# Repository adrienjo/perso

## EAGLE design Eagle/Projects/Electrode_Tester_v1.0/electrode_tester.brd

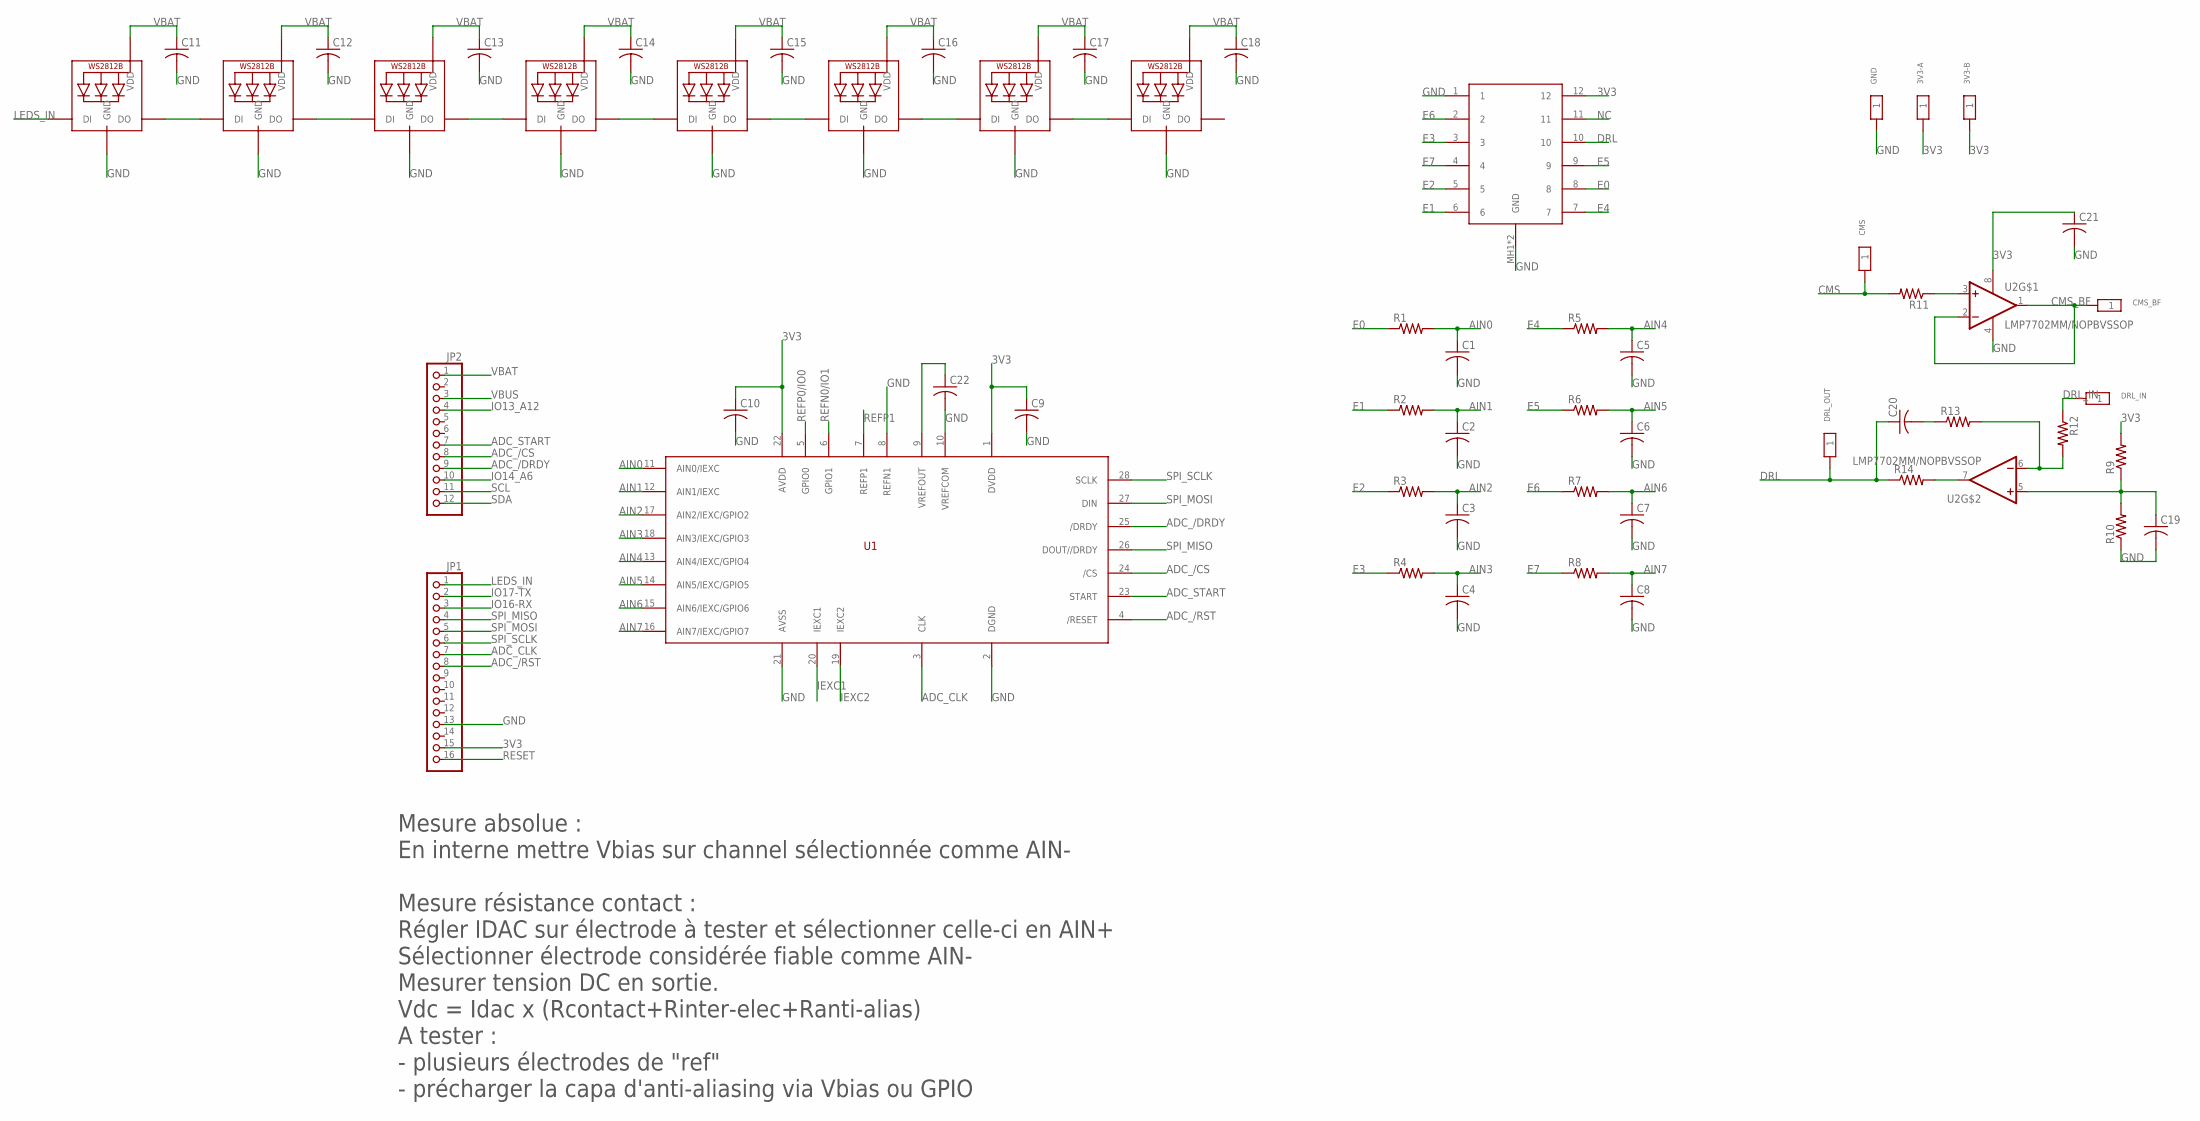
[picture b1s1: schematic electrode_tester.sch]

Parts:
3V3-A, 3V3-B: TESTPAD_PROG; TP1.5MM
C1, C2, C3, C4, C5, C6, C7, C8, C9, C10, C11, C12, C13, C14, C15, C16, C17, C18, C19, C20, C21, C22: C-USC0603; C0603
CMS: TESTPAD_PROG; TP1.5MM
CMS_BF: TESTPAD_PROG; TP1.5MM
CONN1: 505110-1292
DRL_IN: TESTPAD_PROG; TP1.5MM
DRL_OUT: TESTPAD_PROG; TP1.5MM
GND: TESTPAD_PROG; TP1.5MM
JP1: HEADER-1X16ROUND; 1X16_ROUND
JP2: HEADER-1X12; 1X12_ROUND
LED1, LED2, LED3, LED4, LED5, LED6, LED7, LED8: WS2812B5050; WS2812B
R1, R2, R3, R4, R5, R6, R7, R8, R9, R10, R11, R12, R13, R14: R-US_R0603; R0603
U1: ADS1248; TSSOP28
U2: LMP7702MM/NOPBVSSOP; VSSOP8

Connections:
3V3: 3V3-A.1, 3V3-B.1, C9.1, C10.1, C21.1, CONN1.12, JP1.15, R9.2, U1.1 (DVDD), U1.22 (AVDD), U2.8 (V+)
ADC_/CS: JP2.8, U1.24 (/CS)
ADC_/DRDY: JP2.9, U1.25 (/DRDY)
ADC_/RST: JP1.8, U1.4 (/RESET)
ADC_CLK: JP1.7, U1.3 (CLK)
ADC_START: JP2.7, U1.23 (START)
AIN0: C1.1, R1.2, U1.11 (AIN0/IEXC)
AIN1: C2.1, R2.2, U1.12 (AIN1/IEXC)
AIN2: C3.1, R3.2, U1.17 (AIN2/IEXC/GPIO2)
AIN3: C4.1, R4.2, U1.18 (AIN3/IEXC/GPIO3)
AIN4: C5.1, R5.2, U1.13 (AIN4/IEXC/GPIO4)
AIN5: C6.1, R6.2, U1.14 (AIN5/IEXC/GPIO5)
AIN6: C7.1, R7.2, U1.15 (AIN6/IEXC/GPIO6)
AIN7: C8.1, R8.2, U1.16 (AIN7/IEXC/GPIO7)
CMS: CMS.1, R11.2
CMS_BF: CMS_BF.1, U2.1 (OUT), U2.2 (-IN)
DRL: C20.1, CONN1.10, DRL_OUT.1, R14.1
DRL_IN: DRL_IN.1, R12.1
E0: CONN1.8, R1.1
E1: CONN1.6, R2.1
E2: CONN1.5, R3.1
E3: CONN1.3, R4.1
E4: CONN1.7, R5.1
E5: CONN1.9, R6.1
E6: CONN1.2, R7.1
E7: CONN1.4, R8.1
GND: C1.2, C2.2, C3.2, C4.2, C5.2, C6.2, C7.2, C8.2, C9.2, C10.2, C11.2, C12.2, C13.2, C14.2, C15.2, C16.2, C17.2, C18.2, C19.2, C21.2, C22.2, CONN1.1, CONN1.MH1 (GND), CONN1.MH2 (GND), GND.1, JP1.13, LED1.3-GND (GND), LED2.3-GND (GND), LED3.3-GND (GND), LED4.3-GND (GND), LED5.3-GND (GND), LED6.3-GND (GND), LED7.3-GND (GND), LED8.3-GND (GND), R10.1, U1.2 (DGND), U1.8 (REFN1), U1.10 (VREFCOM), U1.21 (AVSS), U2.4 (V-)
IEXC1: U1.20 (IEXC1)
IEXC2: U1.19 (IEXC2)
IO13_A12: JP2.4
IO14_A6: JP2.10
IO16-RX: JP1.3
IO17-TX: JP1.2
LEDS_IN: JP1.1, LED1.4-DIN (DI)
unnamed: LED1.2-DOUT (DO), LED2.4-DIN (DI)
unnamed: LED2.2-DOUT (DO), LED3.4-DIN (DI)
unnamed: LED3.2-DOUT (DO), LED4.4-DIN (DI)
unnamed: LED4.2-DOUT (DO), LED5.4-DIN (DI)
unnamed: LED5.2-DOUT (DO), LED6.4-DIN (DI)
unnamed: LED6.2-DOUT (DO), LED7.4-DIN (DI)
unnamed: LED7.2-DOUT (DO), LED8.4-DIN (DI)
unnamed: R11.1, U2.3 (+IN)
unnamed: C22.1, U1.9 (VREFOUT)
unnamed: R12.2, R13.2, U2.6 (-IN)
unnamed: C20.2, R13.1
unnamed: R14.2, U2.7 (OUT)
unnamed: C19.1, R9.1, R10.2, U2.5 (+IN)
NC: CONN1.11
REFN0/IO1: U1.6 (GPIO1)
REFP0/IO0: U1.5 (GPIO0)
REFP1: U1.7 (REFP1)
RESET: JP1.16
SCL: JP2.11
SDA: JP2.12
SPI_MISO: JP1.4, U1.26 (DOUT//DRDY)
SPI_MOSI: JP1.5, U1.27 (DIN)
SPI_SCLK: JP1.6, U1.28 (SCLK)
VBAT: C11.1, C12.1, C13.1, C14.1, C15.1, C16.1, C17.1, C18.1, JP2.1, LED1.1-VDD (VDD), LED2.1-VDD (VDD), LED3.1-VDD (VDD), LED4.1-VDD (VDD), LED5.1-VDD (VDD), LED6.1-VDD (VDD), LED7.1-VDD (VDD), LED8.1-VDD (VDD)
VBUS: JP2.3

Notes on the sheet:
Mesure absolue : En interne mettre Vbias sur channel sélectionnée comme AIN- Mesure résistance contact : Régler IDAC sur électrode à tester et sélectionner celle-ci en AIN+ Sélectionner électrode considérée fiable comme AIN- Mesurer tension DC en sortie. Vdc = Idac x (Rcontact+Rinter-elec+Ranti-ali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

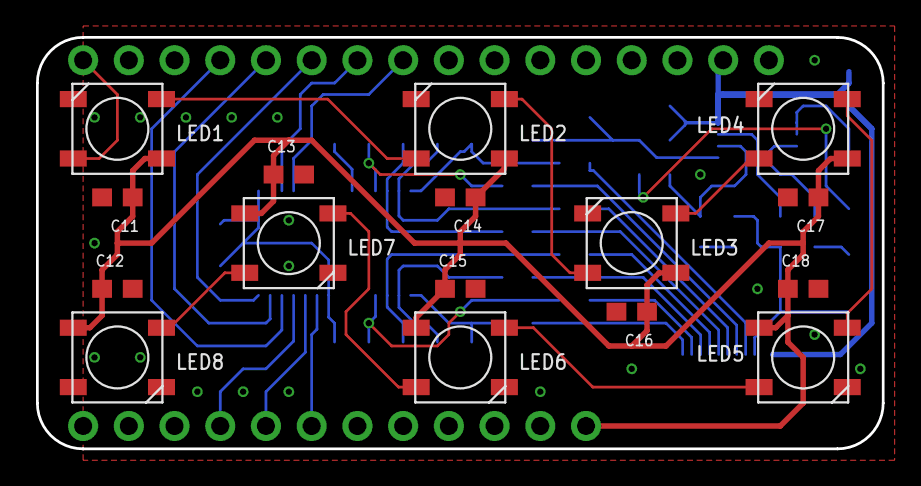
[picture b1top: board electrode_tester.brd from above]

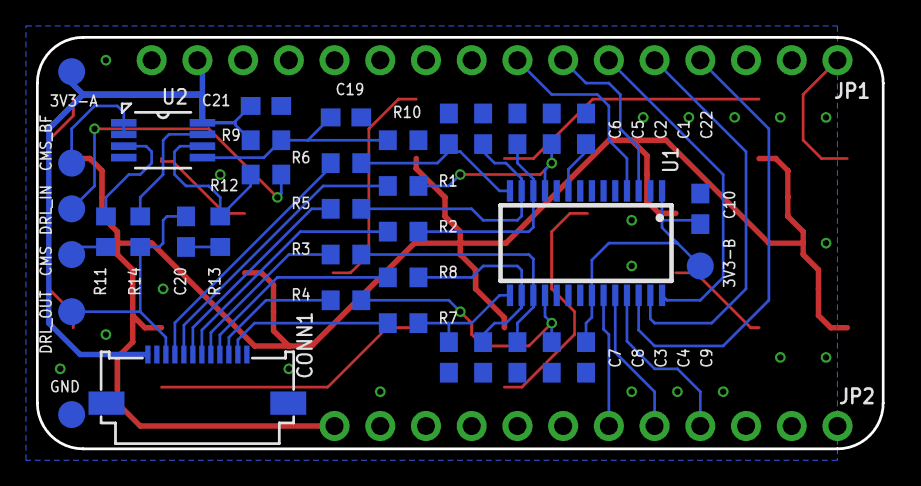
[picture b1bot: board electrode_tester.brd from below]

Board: 2 copper layers, 47.0 x 22.9 mm, 56 parts (40 on the bottom side), 45 nets.

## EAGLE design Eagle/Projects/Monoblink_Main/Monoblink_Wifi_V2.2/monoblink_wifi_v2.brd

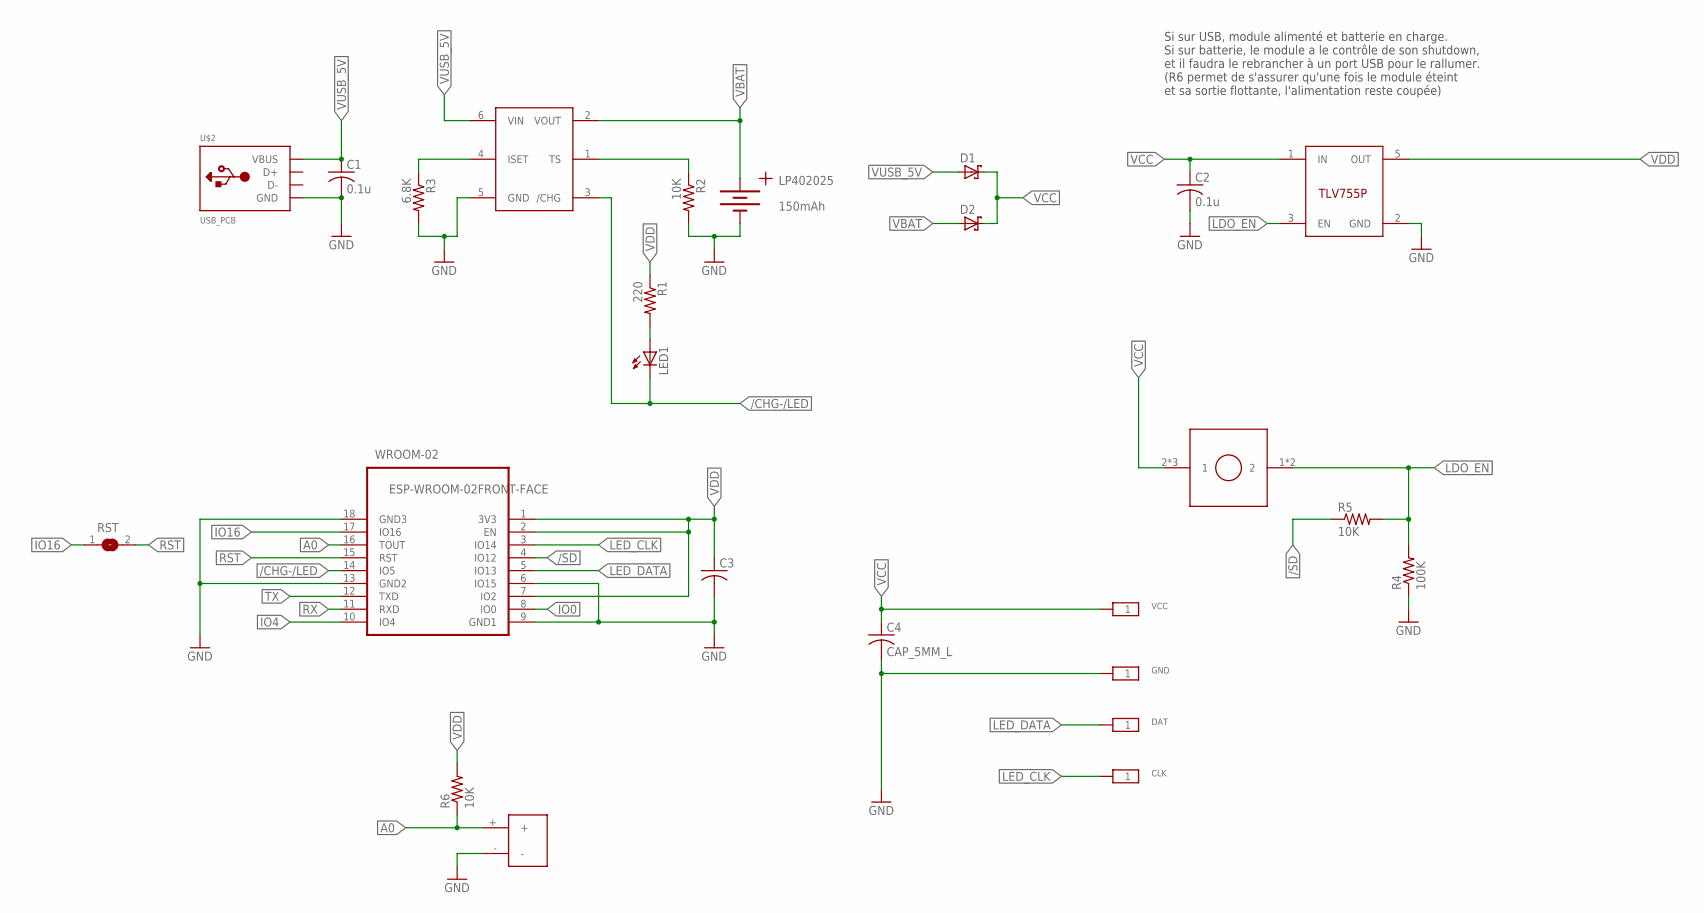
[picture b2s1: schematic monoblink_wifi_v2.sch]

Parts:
C1, C2: 0.1u; C0603
C3: C-USC0603; C0603
C4: CAP_5MM_L; TT2D5L
CHG: BQ21040; SOT23-6
CLK: TESTPAD_PROGSPRING_PIN; MATRIX_CONN
D1, D2: NSR0320MW2T1G; SOD323
DAT: TESTPAD_PROGSPRING_PIN; MATRIX_CONN
GND: TESTPAD_PROGSPRING_PIN; MATRIX_CONN
LDO: TLV755P; SOT23-5
LED1: LEDCHIP-LED0603; CHIP-LED0603
LP402025: 150mAh; BATT_CON
ON/OFF: KMS231GPLFSNO_PEGS; KMS231GLFS
R1: 220; R0603
R2, R5, R6: 10K; R0603
R3: 6.8K; R0603
R4: 100K; R0603
RST: SOLDERJUMPER; SOLDERJUMPER_ARROW_NOPASTE
U$1: 2PIN_STD
U$2: USB_PCB; USB_PADS
VCC: TESTPAD_PROGSPRING_PIN; MATRIX_CONN
WROOM-02: ESP-WROOM-02FRONT-FACE; FRONT-FACE

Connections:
/CHG-/LED: CHG.3 (/CHG), LED1.C, WROOM-02.14 (IO5)
/SD: R5.1, WROOM-02.4 (IO12)
A0: R6.1, U$1.+, WROOM-02.16 (TOUT)
GND: C1.2, C2.2, C3.2, C4.- (2), CHG.5 (GND), GND.1, LDO.2 (GND), LP402025.V- (-), R2.2, R3.2, R4.1, U$1.-, U$2.GND, WROOM-02.6 (IO15), WROOM-02.9 (GND1), WROOM-02.13 (GND2), WROOM-02.18 (GND3)
IO0: WROOM-02.8 (IO0)
IO4: WROOM-02.10 (IO4)
IO16: RST.1, WROOM-02.17 (IO16)
ISET: CHG.4 (ISET), R3.1
LDO_EN: LDO.3 (EN), ON/OFF.1 (2), ON/OFF.5 (2), R4.2, R5.2
LED_CLK: CLK.1, WROOM-02.3 (IO14)
LED_DATA: DAT.1, WROOM-02.5 (IO13)
unnamed: LED1.A, R1.2
RST: RST.2, WROOM-02.15 (RST)
RX: WROOM-02.11 (RXD)
TS: CHG.1 (TS), R2.1
TX: WROOM-02.12 (TXD)
VBAT: CHG.2 (VOUT), D2.2 (A), LP402025.V+ (+)
VCC: C2.1, C4.+ (1), D1.1 (C), D2.1 (C), LDO.1 (IN), ON/OFF.2 (1), ON/OFF.3 (1), ON/OFF.4 (1), VCC.1
VDD: C3.1, LDO.5 (OUT), R1.1, R6.2, WROOM-02.1 (3V3), WROOM-02.2 (EN), WROOM-02.7 (IO2)
VUSB_5V: C1.1, CHG.6 (VIN), D1.2 (A), U$2.V_SUPPLY (VBUS)

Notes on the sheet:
Si sur USB, module alimenté et batterie en charge. Si sur batterie, le module a le contrôle de son shutdown, et il faudra le rebrancher à un port USB pour le rallumer. (R6 permet de s'assurer qu'une fois le module éteint et sa sortie flottante, l'alimentation reste coupée)

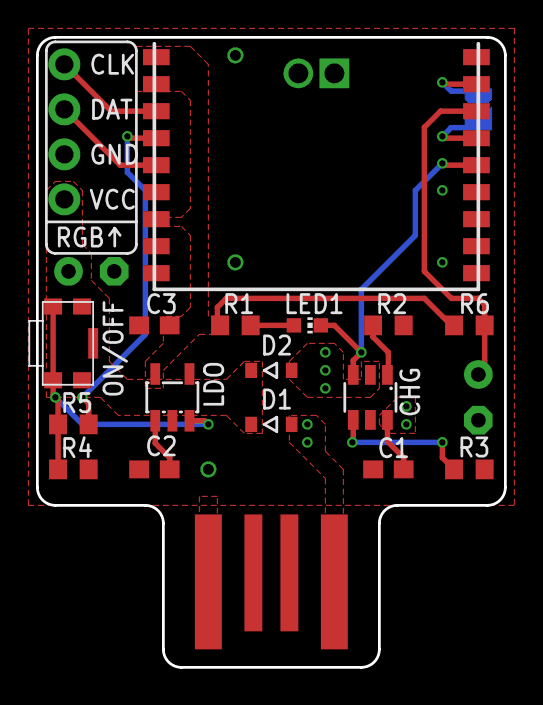
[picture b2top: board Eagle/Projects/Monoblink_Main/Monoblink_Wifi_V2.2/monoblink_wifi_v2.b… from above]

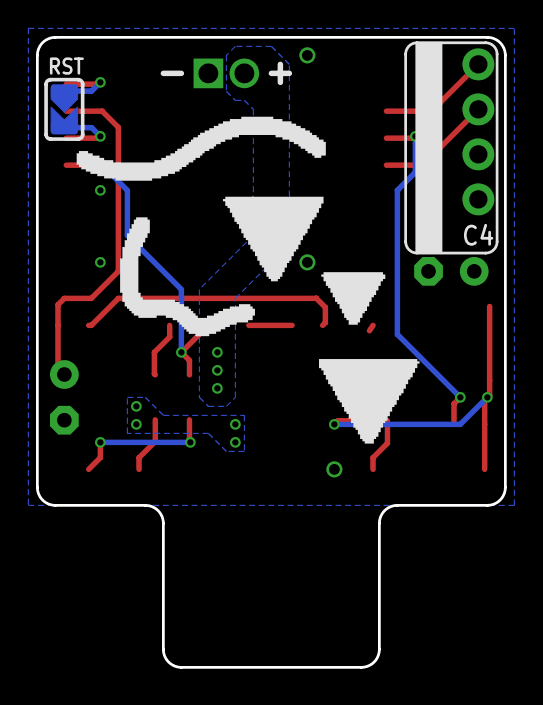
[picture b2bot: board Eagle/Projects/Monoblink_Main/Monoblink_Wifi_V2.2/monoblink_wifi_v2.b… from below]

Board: 2 copper layers, 26.0 x 35.0 mm, 25 parts (2 on the bottom side), 16 nets.

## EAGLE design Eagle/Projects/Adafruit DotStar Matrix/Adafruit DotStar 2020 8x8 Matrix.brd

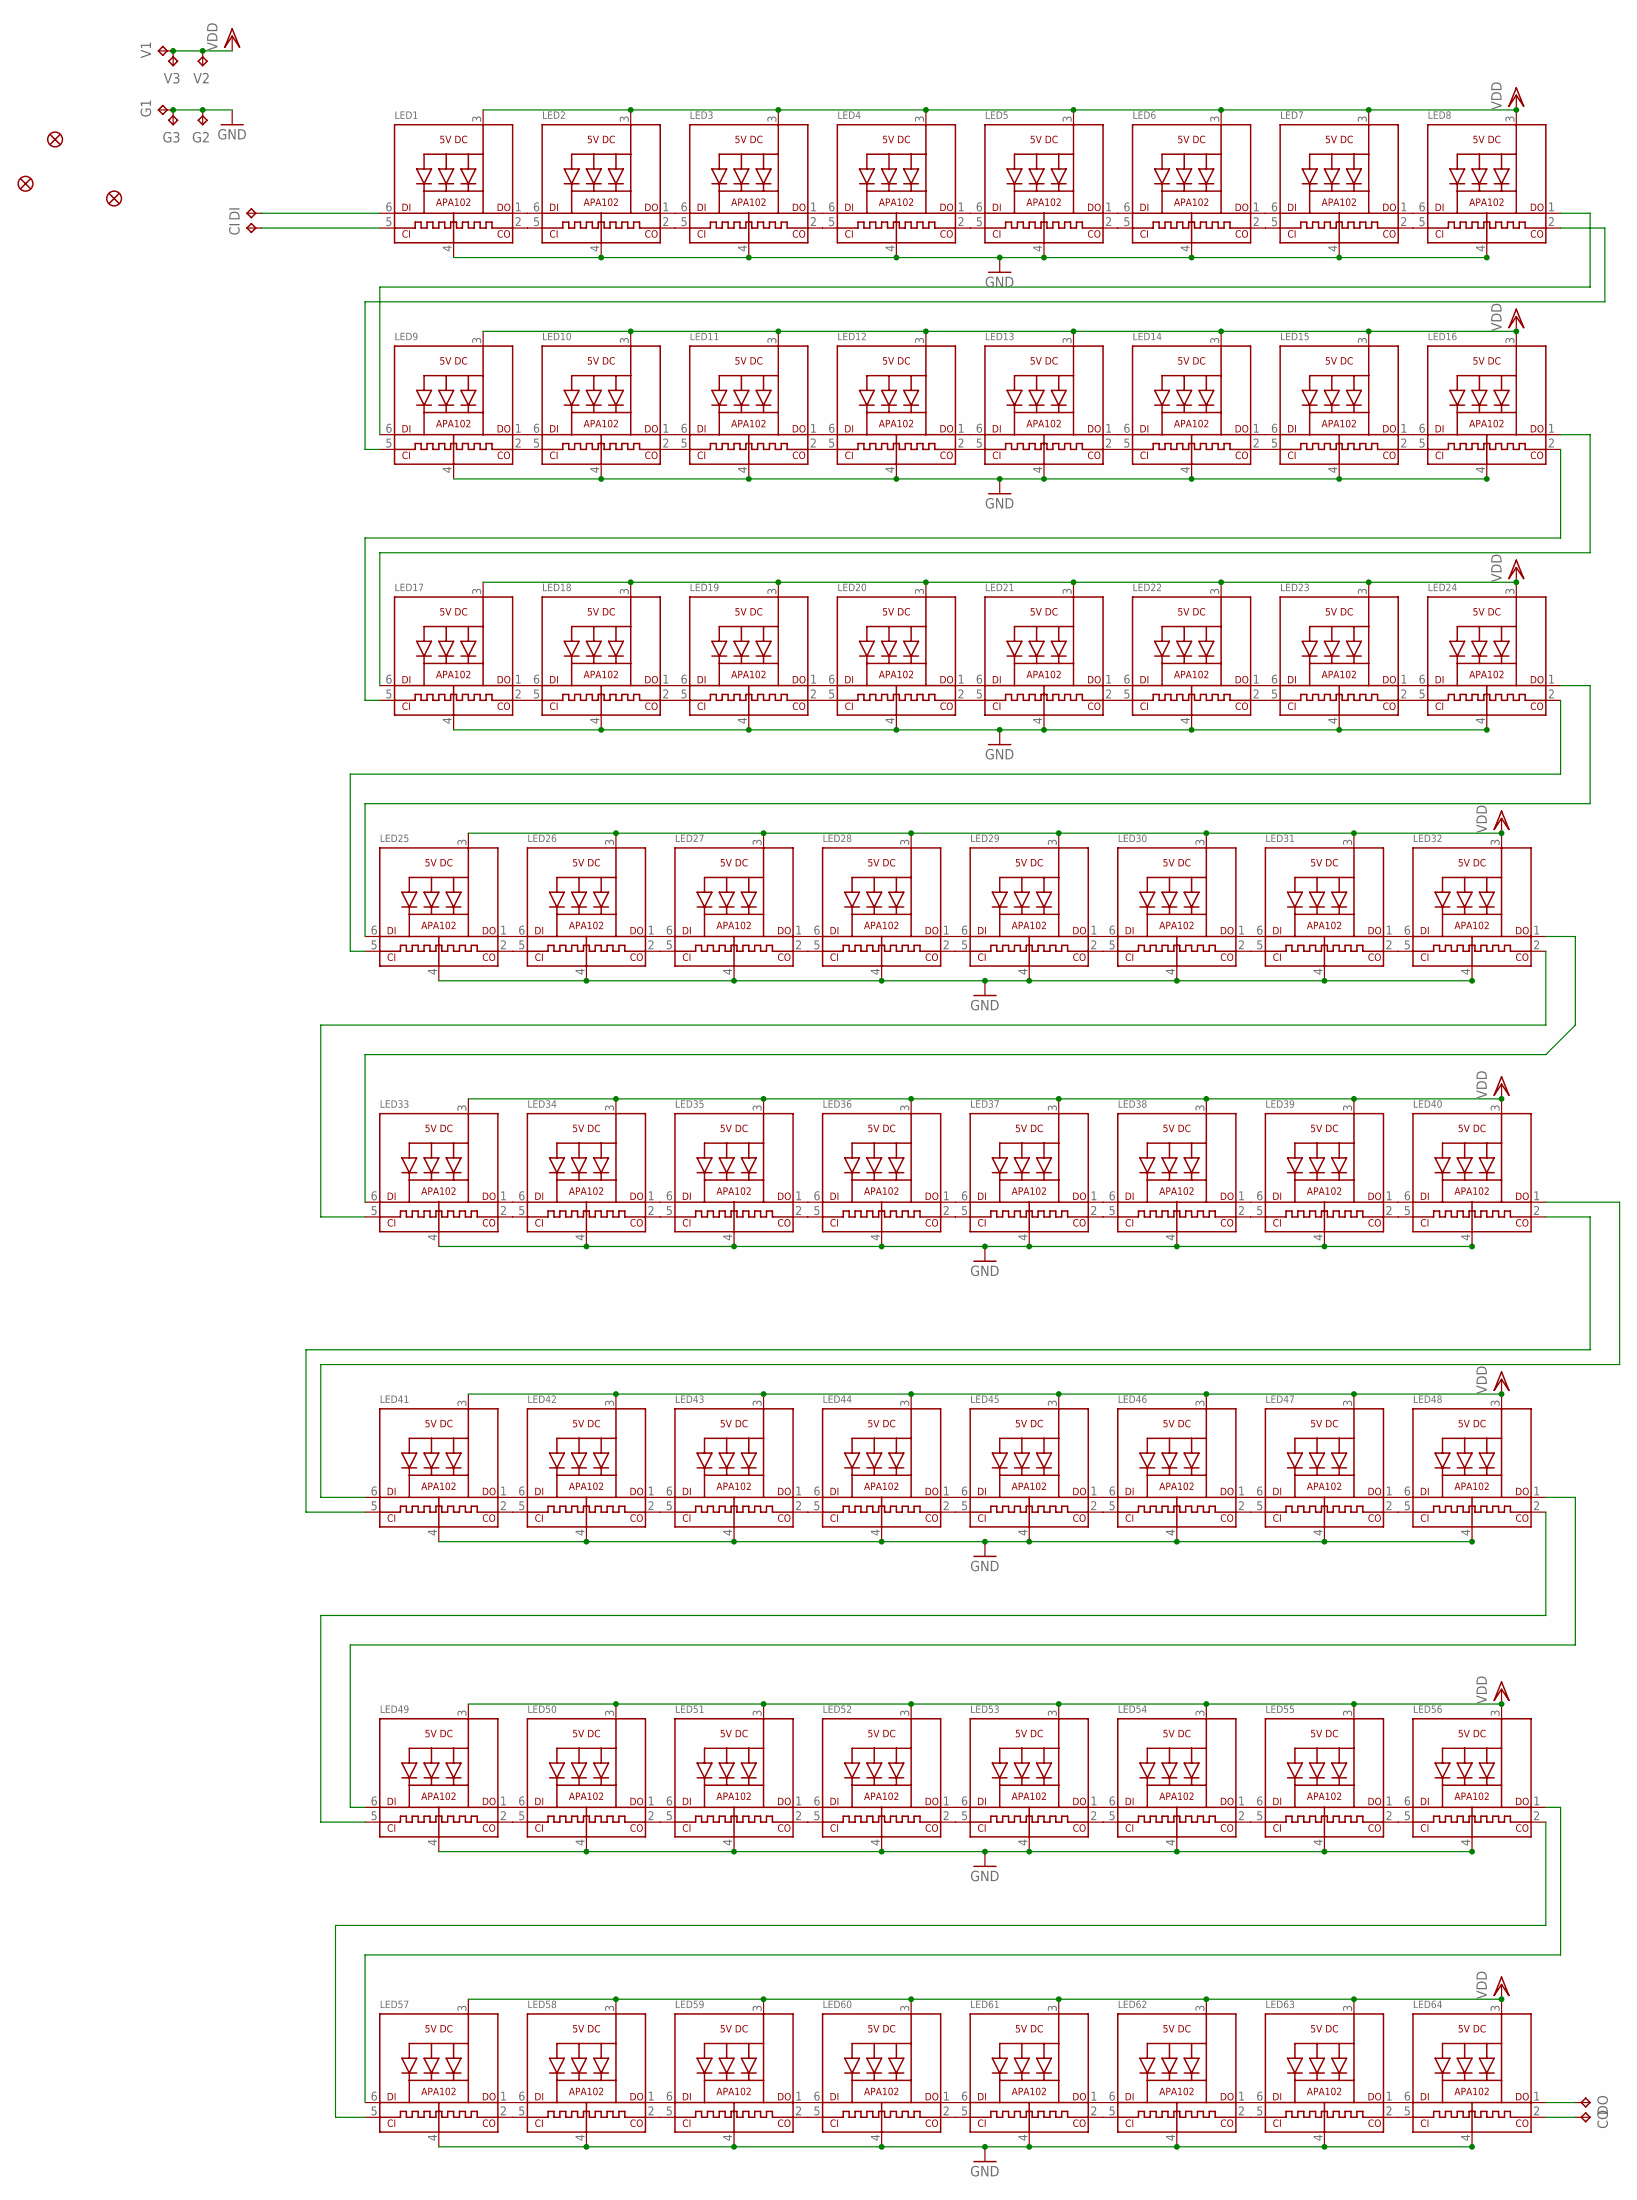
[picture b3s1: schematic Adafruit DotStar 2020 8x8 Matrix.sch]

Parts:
CI: TPTP20R; TP20R
CO: TPTP20R; TP20R
DI: TPTP20R; TP20R
DO: TPTP20R; TP20R
FID1, FID2, FID3: FIDUCIAL_0.5MM
G1, G2, G3: TPTP20R; TP20R
LED1, LED2, LED3, LED4, LED5, LED6, LED7, LED8, LED9, LED10, LED11, LED12, LED13, LED14, LED15, LED16, LED17, LED18, LED19, LED20, LED21, LED22, LED23, LED24, LED25, LED26, LED27, LED28, LED29, LED30, LED31, LED32, LED33, LED34, LED35, LED36, LED37, LED38, LED39, LED40, LED41, LED42, LED43, LED44, LED45, LED46, LED47, LED48, LED49, LED50, LED51, LED52, LED53, LED54, LED55, LED56, LED57, LED58, LED59, LED60, LED61, LED62, LED63, LED64: APA1022020; APA102_2020
V1, V2, V3: TPTP20R; TP20R

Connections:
C0: CO.TP, LED64.2 (CKO)
CIN: CI.TP, LED1.5 (CKI)
D0: DO.TP, LED64.1 (DO)
DIN: DI.TP, LED1.6 (DI)
GND: G1.TP, G2.TP, G3.TP, LED1.4 (GND), LED2.4 (GND), LED3.4 (GND), LED4.4 (GND), LED5.4 (GND), LED6.4 (GND), LED7.4 (GND), LED8.4 (GND), LED9.4 (GND), LED10.4 (GND), LED11.4 (GND), LED12.4 (GND), LED13.4 (GND), LED14.4 (GND), LED15.4 (GND), LED16.4 (GND), LED17.4 (GND), LED18.4 (GND), LED19.4 (GND), LED20.4 (GND), LED21.4 (GND), LED22.4 (GND), LED23.4 (GND), LED24.4 (GND), LED25.4 (GND), LED26.4 (GND), LED27.4 (GND), LED28.4 (GND), LED29.4 (GND), LED30.4 (GND), LED31.4 (GND), LED32.4 (GND), LED33.4 (GND), LED34.4 (GND), LED35.4 (GND), LED36.4 (GND), LED37.4 (GND), LED38.4 (GND), LED39.4 (GND), LED40.4 (GND), LED41.4 (GND), LED42.4 (GND), LED43.4 (GND), LED44.4 (GND), LED45.4 (GND), LED46.4 (GND), LED47.4 (GND), LED48.4 (GND), LED49.4 (GND), LED50.4 (GND), LED51.4 (GND), LED52.4 (GND), LED53.4 (GND), LED54.4 (GND), LED55.4 (GND), LED56.4 (GND), LED57.4 (GND), LED58.4 (GND), LED59.4 (GND), LED60.4 (GND), LED61.4 (GND), LED62.4 (GND), LED63.4 (GND), LED64.4 (GND)
unnamed: LED1.1 (DO), LED2.6 (DI)
unnamed: LED1.2 (CKO), LED2.5 (CKI)
unnamed: LED2.1 (DO), LED3.6 (DI)
unnamed: LED2.2 (CKO), LED3.5 (CKI)
unnamed: LED3.1 (DO), LED4.6 (DI)
unnamed: LED3.2 (CKO), LED4.5 (CKI)
unnamed: LED4.1 (DO), LED5.6 (DI)
unnamed: LED4.2 (CKO), LED5.5 (CKI)
unnamed: LED5.1 (DO), LED6.6 (DI)
unnamed: LED5.2 (CKO), LED6.5 (CKI)
unnamed: LED6.1 (DO), LED7.6 (DI)
unnamed: LED6.2 (CKO), LED7.5 (CKI)
unnamed: LED7.1 (DO), LED8.6 (DI)
unnamed: LED7.2 (CKO), LED8.5 (CKI)
unnamed: LED9.1 (DO), LED10.6 (DI)
unnamed: LED9.2 (CKO), LED10.5 (CKI)
unnamed: LED10.1 (DO), LED11.6 (DI)
unnamed: LED10.2 (CKO), LED11.5 (CKI)
unnamed: LED11.1 (DO), LED12.6 (DI)
unnamed: LED11.2 (CKO), LED12.5 (CKI)
unnamed: LED12.1 (DO), LED13.6 (DI)
unnamed: LED12.2 (CKO), LED13.5 (CKI)
unnamed: LED13.1 (DO), LED14.6 (DI)
unnamed: LED13.2 (CKO), LED14.5 (CKI)
unnamed: LED14.1 (DO), LED15.6 (DI)
unnamed: LED14.2 (CKO), LED15.5 (CKI)
unnamed: LED15.1 (DO), LED16.6 (DI)
unnamed: LED15.2 (CKO), LED16.5 (CKI)
unnamed: LED17.1 (DO), LED18.6 (DI)
unnamed: LED17.2 (CKO), LED18.5 (CKI)
unnamed: LED18.1 (DO), LED19.6 (DI)
unnamed: LED18.2 (CKO), LED19.5 (CKI)
unnamed: LED19.1 (DO), LED20.6 (DI)
unnamed: LED19.2 (CKO), LED20.5 (CKI)
unnamed: LED20.1 (DO), LED21.6 (DI)
unnamed: LED20.2 (CKO), LED21.5 (CKI)
unnamed: LED21.1 (DO), LED22.6 (DI)
unnamed: LED21.2 (CKO), LED22.5 (CKI)
unnamed: LED22.1 (DO), LED23.6 (DI)
unnamed: LED22.2 (CKO), LED23.5 (CKI)
unnamed: LED23.1 (DO), LED24.6 (DI)
unnamed: LED23.2 (CKO), LED24.5 (CKI)
unnamed: LED25.1 (DO), LED26.6 (DI)
unnamed: LED25.2 (CKO), LED26.5 (CKI)
unnamed: LED26.1 (DO), LED27.6 (DI)
unnamed: LED26.2 (CKO), LED27.5 (CKI)
unnamed: LED27.1 (DO), LED28.6 (DI)
unnamed: LED27.2 (CKO), LED28.5 (CKI)
unnamed: LED28.1 (DO), LED29.6 (DI)
unnamed: LED28.2 (CKO), LED29.5 (CKI)
unnamed: LED29.1 (DO), LED30.6 (DI)
unnamed: LED29.2 (CKO), LED30.5 (CKI)
unnamed: LED30.1 (DO), LED31.6 (DI)
unnamed: LED30.2 (CKO), LED31.5 (CKI)
unnamed: LED31.1 (DO), LED32.6 (DI)
unnamed: LED31.2 (CKO), LED32.5 (CKI)
unnamed: LED33.1 (DO), LED34.6 (DI)
unnamed: LED33.2 (CKO), LED34.5 (CKI)
unnamed: LED34.1 (DO), LED35.6 (DI)
unnamed: LED34.2 (CKO), LED35.5 (CKI)
unnamed: LED35.1 (DO), LED36.6 (DI)
unnamed: LED35.2 (CKO), LED36.5 (CKI)
unnamed: LED36.1 (DO), LED37.6 (DI)
unnamed: LED36.2 (CKO), LED37.5 (CKI)
unnamed: LED37.1 (DO), LED38.6 (DI)
unnamed: LED37.2 (CKO), LED38.5 (CKI)
unnamed: LED38.1 (DO), LED39.6 (DI)
unnamed: LED38.2 (CKO), LED39.5 (CKI)
unnamed: LED39.1 (DO), LED40.6 (DI)
unnamed: LED39.2 (CKO), LED40.5 (CKI)
unnamed: LED41.1 (DO), LED42.6 (DI)
unnamed: LED41.2 (CKO), LED42.5 (CKI)
unnamed: LED42.1 (DO), LED43.6 (DI)
unnamed: LED42.2 (CKO), LED43.5 (CKI)
unnamed: LED43.1 (DO), LED44.6 (DI)
unnamed: LED43.2 (CKO), LED44.5 (CKI)
unnamed: LED44.1 (DO), LED45.6 (DI)
unnamed: LED44.2 (CKO), LED45.5 (CKI)
unnamed: LED45.1 (DO), LED46.6 (DI)
unnamed: LED45.2 (CKO), LED46.5 (CKI)
unnamed: LED46.1 (DO), LED47.6 (DI)
unnamed: LED46.2 (CKO), LED47.5 (CKI)
unnamed: LED47.1 (DO), LED48.6 (DI)
unnamed: LED47.2 (CKO), LED48.5 (CKI)
unnamed: LED49.1 (DO), LED50.6 (DI)
unnamed: LED49.2 (CKO), LED50.5 (CKI)
unnamed: LED50.1 (DO), LED51.6 (DI)
unnamed: LED50.2 (CKO), LED51.5 (CKI)
unnamed: LED51.1 (DO), LED52.6 (DI)
unnamed: LED51.2 (CKO), LED52.5 (CKI)
unnamed: LED52.1 (DO), LED53.6 (DI)
unnamed: LED52.2 (CKO), LED53.5 (CKI)
unnamed: LED53.1 (DO), LED54.6 (DI)
unnamed: LED53.2 (CKO), LED54.5 (CKI)
unnamed: LED54.1 (DO), LED55.6 (DI)
unnamed: LED54.2 (CKO), LED55.5 (CKI)
unnamed: LED55.1 (DO), LED56.6 (DI)
unnamed: LED55.2 (CKO), LED56.5 (CKI)
unnamed: LED57.1 (DO), LED58.6 (DI)
unnamed: LED57.2 (CKO), LED58.5 (CKI)
unnamed: LED58.1 (DO), LED59.6 (DI)
unnamed: LED58.2 (CKO), LED59.5 (CKI)
unnamed: LED59.1 (DO), LED60.6 (DI)
unnamed: LED59.2 (CKO), LED60.5 (CKI)
unnamed: LED60.1 (DO), LED61.6 (DI)
unnamed: LED60.2 (CKO), LED61.5 (CKI)
unnamed: LED61.1 (DO), LED62.6 (DI)
unnamed: LED61.2 (CKO), LED62.5 (CKI)
unnamed: LED62.1 (DO), LED63.6 (DI)
unnamed: LED62.2 (CKO), LED63.5 (CKI)
unnamed: LED63.1 (DO), LED64.6 (DI)
unnamed: LED63.2 (CKO), LED64.5 (CKI)
unnamed: LED8.1 (DO), LED9.6 (DI)
unnamed: LED8.2 (CKO), LED9.5 (CKI)
unnamed: LED16.1 (DO), LED17.6 (DI)
unnamed: LED16.2 (CKO), LED17.5 (CKI)
unnamed: LED24.1 (DO), LED25.6 (DI)
unnamed: LED24.2 (CKO), LED25.5 (CKI)
unnamed: LED32.1 (DO), LED33.6 (DI)
unnamed: LED32.2 (CKO), LED33.5 (CKI)
unnamed: LED56.1 (DO), LED57.6 (DI)
unnamed: LED56.2 (CKO), LED57.5 (CKI)
unnamed: LED48.2 (CKO), LED49.5 (CKI)
unnamed: LED48.1 (DO), LED49.6 (DI)
unnamed: LED40.2 (CKO), LED41.5 (CKI)
unnamed: LED40.1 (DO), LED41.6 (DI)
VDD: LED1.3 (VDD), LED2.3 (VDD), LED3.3 (VDD), LED4.3 (VDD), LED5.3 (VDD), LED6.3 (VDD), LED7.3 (VDD), LED8.3 (VDD), LED9.3 (VDD), LED10.3 (VDD), LED11.3 (VDD), LED12.3 (VDD), LED13.3 (VDD), LED14.3 (VDD), LED15.3 (VDD), LED16.3 (VDD), LED17.3 (VDD), LED18.3 (VDD), LED19.3 (VDD), LED20.3 (VDD), LED21.3 (VDD), LED22.3 (VDD), LED23.3 (VDD), LED24.3 (VDD), LED25.3 (VDD), LED26.3 (VDD), LED27.3 (VDD), LED28.3 (VDD), LED29.3 (VDD), LED30.3 (VDD), LED31.3 (VDD), LED32.3 (VDD), LED33.3 (VDD), LED34.3 (VDD), LED35.3 (VDD), LED36.3 (VDD), LED37.3 (VDD), LED38.3 (VDD), LED39.3 (VDD), LED40.3 (VDD), LED41.3 (VDD), LED42.3 (VDD), LED43.3 (VDD), LED44.3 (VDD), LED45.3 (VDD), LED46.3 (VDD), LED47.3 (VDD), LED48.3 (VDD), LED49.3 (VDD), LED50.3 (VDD), LED51.3 (VDD), LED52.3 (VDD), LED53.3 (VDD), LED54.3 (VDD), LED55.3 (VDD), LED56.3 (VDD), LED57.3 (VDD), LED58.3 (VDD), LED59.3 (VDD), LED60.3 (VDD), LED61.3 (VDD), LED62.3 (VDD), LED63.3 (VDD), LED64.3 (VDD), V1.TP, V2.TP, V3.TP

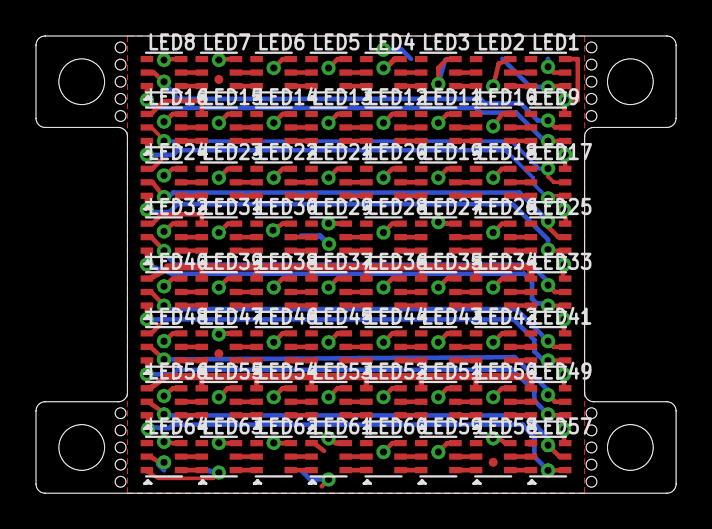
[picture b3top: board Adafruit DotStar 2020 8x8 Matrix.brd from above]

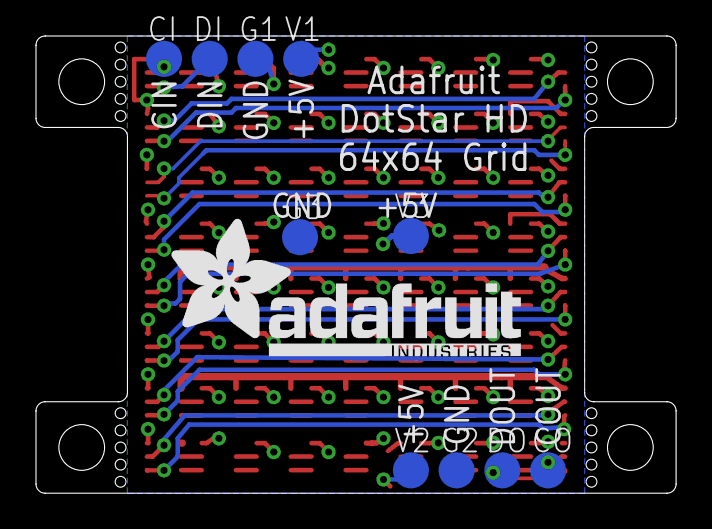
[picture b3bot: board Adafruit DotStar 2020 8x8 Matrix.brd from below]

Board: 2 copper layers, 35.6 x 25.4 mm, 78 parts (11 on the bottom side), 132 nets.

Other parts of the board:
U$1: ADAFRUIT_TEXT_20MM

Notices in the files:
parts and their libraries:
microbuilder: This work is placed in the public domain, and may be freely used for commercial and non-commercial work with the following conditions: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
